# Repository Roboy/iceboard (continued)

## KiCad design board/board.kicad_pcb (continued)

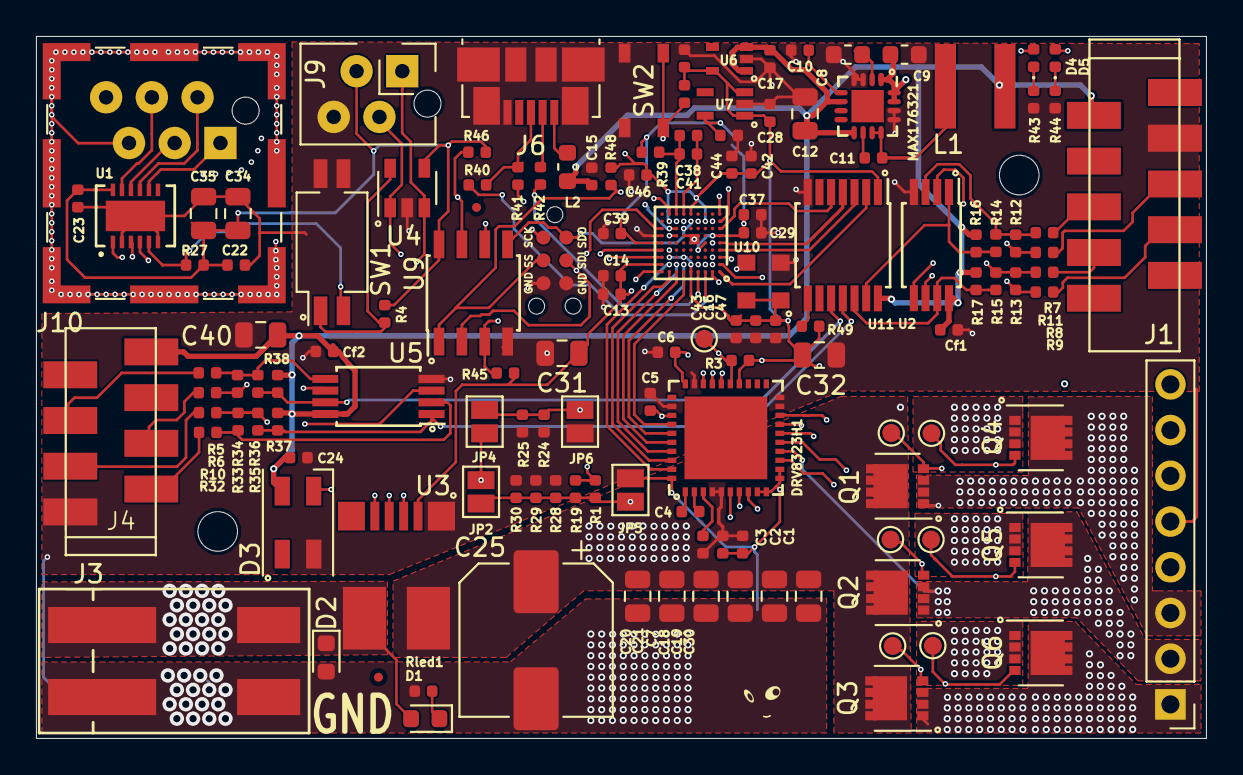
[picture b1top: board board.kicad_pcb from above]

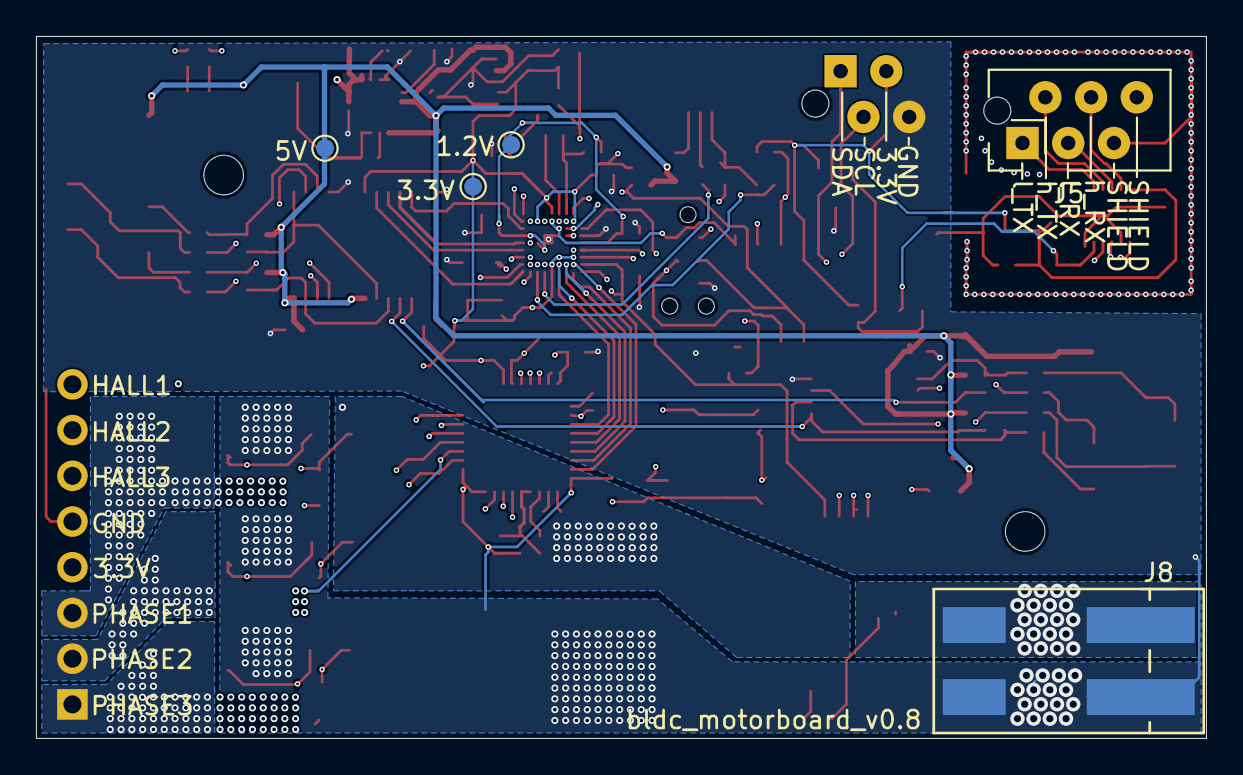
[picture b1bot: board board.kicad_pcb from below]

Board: 4 copper layers, 65.0 x 39.0 mm, 148 parts (5 on the bottom side), 97 nets.

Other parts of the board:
U6#2, U6#3: MIC5504-3.3YM5-TR; SC70-5

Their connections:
+5V: U6#2.1, U6#2.3, U6#3.1, U6#3.3; also elsewhere on the board
GND: U6#2.2, U6#3.2; also elsewhere on the board
unnamed 107: U6#2.4, U6#3.4; also elsewhere on the board

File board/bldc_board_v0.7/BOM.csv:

Id,Designator,Package,Quantity,Designation,Supplier and ref
2,"C35,C34,C32,C31,C40",C_0805_2012Metric,5,100u/6.3V,https://www.mouser.de/ProductDetail/Murata-Electronics/GRM21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
3,U11,TSSOP-14_4.4x5mm_P0.65mm,1,TXB0104PW,https://www.mouser.de/ProductDetail/Texas-Instruments/TXB010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
4,L1,XAL5050-103MEC,1,10uH,https://www.mouser.de/ProductDetail/Coilcraft/XAL5050-103MEC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
6,U8,iCE40-PL9K-CM81,1,iCE40-LP8K-CM81,https://www.mouser.de/ProductDetail/Lattice/iCE40LP8K-CM81?q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
7,J4,micro_match_female_8pos_SMT,1,ENCODER1,https://www.mouser.de/ProductDetail/?qs=tddCKBGf4%252BORyb3A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
8,DRV8323H1,QFN-40-1EP_6x6mm_Pitch0.5mm,1,DRV8323HRTA,https://www.mouser.de/ProductDetail/Texas-Instruments/DRV832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
9,"U2,U5",TSSOP-8_4.4x3mm_P0.65mm,2,LM2903,https://www.mouser.de/ProductDetail/Texas-Instruments/LM2903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
10,"Q2,Q1,Q4,Q5,Q3,Q6",VSON-8_3.3x3.3mm_P0.65mm_NexFET,6,BSZ100N06NS,https://www.mouser.de/ProductDetail/Infineon-Technologies/BS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
11,U1,ltc2855,1,LTC2855CDEPBF,https://www.mouser.de/ProductDetail/Analog-Devices/LTC2855CD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
13,"R27,R15,R14,R4,Rled1,R3,R35,R36,R45,R46,R48,R49,R47",R_0402_1005Metric,21,10k,
14,"C23,C22,C11,Cf1,C6,C2,C24,Cf2,C13,C14,C16,C29,C41,C44,C46,C47",C_0402_1005Metric,16,0.1uF,https://www.mouser.de/ProductDetail/Wurth-Elektronik/8850121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
15,"C21,C19,C18,C27,C20,C7,C30",C_0805_2012Metric,7,22uF/35V,https://www.mouser.de/ProductDetail/TDK/C2012JB1V226M125AC?q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
17,C25,CP_Elec_6.3x4.5,1,220uF,https://www.mouser.de/ProductDetail/Nichicon/UUR1V221MNL6GS?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
18,"C8,C9",C_0603_1608Metric,2,2.2uF,https://www.mouser.de/ProductDetail/Murata-Electronics/GRM18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
19,C12,C_0805_2012Metric,1,22uF,https://www.mouser.de/ProductDetail/KEMET/C0805C226M9PACTU?q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
20,MAX176321,QFN-16-1EP_3x3mm_Pitch0.5mm,1,MAX17632,https://www.mouser.de/ProductDetail/Maxim-Integrated/MAX1763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
21,C10,C_0402_1005Metric,1,5600pF,
22,"R11,R10,R9,R8,R7,R6,R5,R32,R17,R16,R37,R38",R_0402_1005Metric,8,1k,
23,D2,D_0603_1608Metric,1,D_TVS,https://www.mouser.de/ProductDetail/Comchip-Technology/CPDU2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
26,J3,Wago_2060_2_SMD,1,POWER_IN,https://www.reichelt.com/de/en/smd-pcb-terminal-2-pole-rm-4-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
28,"C5,C3,C17,C26,C28,C36",C_0402_1005Metric,6,1uF,
29,C4,C_0402_1005Metric,1,47nF,
30,"C1,C15,C38",C_0402_1005Metric,3,10uF,https://www.mouser.de/ProductDetail/Taiyo-Yuden/GMK316BBJ106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
32,D3,LED_SK6812MINI_PLCC4_3.5x3.5mm_P1.75mm,1,SK6812MINI,https://www.aliexpress.com/item/32434844290.html
38,U3,TLI4970,1,TLI4970,https://www.mouser.de/ProductDetail/Infineon-Technologies/TL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
44,J1,micro_match_female_10pos_SMT,1,ENCODER0,https://www.mouser.de/ProductDetail/TE-Connectivity/1-217871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
45,R39,R_0402_1005Metric,1,100,
46,R40,R_0402_1005Metric,1,1.5k,
47,"R41,R42",R_0402_1005Metric,2,68,
48,"R43,R44",R_0402_1005Metric,2,270,
49,U4,SOT-23-5,1,EEPROM,https://www.mouser.de/ProductDetail/Microchip-Technology-Atm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
52,J6,USB_Micro-B_Molex_47346-0001,1,USB_OTG,https://www.mouser.de/ProductDetail/Molex/47346-0001?qs=sGAE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
53,U9,SOIC-8_3.9x4.9mm_P1.27mm,1,AT25SF081-SSHD-B,https://www.mouser.de/ProductDetail/Adesto-Technologies/AT25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
54,SW2,PTS_810_SMT_Switch,1,SW_Push,https://www.mouser.de/ProductDetail/CK/PTS810SJK250SMTRLFS?q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
55,U6,SC70-5,1,MIC5504-3.3YM5-TR,https://www.mouser.de/ProductDetail/595-TLV70033DCKR
56,U7,SC-70-C5,1,MIC5365-1.2YC5-TR,https://www.mouser.de/ProductDetail/Microchip-Technology-Mic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
57,U10,CDFN3225-4LD-PL-1,1,DSC6001CI2A-016.0000T,https://www.mouser.de/ProductDetail/Microchip-Technology/DSC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
58,"C37,C39,C42,C43",C_0402_1005Metric,4,10nF,
59,D1,LED_0603_1608Metric,1,LED,https://www.mouser.de/ProductDetail/ROHM-Semiconductor/SMLD1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
60,L2,L_0603_1608Metric,1,Bead,https://www.mouser.de/ProductDetail/Murata-Electronics/BLM18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
61,SW1,SW_DIP_SPSTx02_Slide_Copal_CHS-02A_W5.08mm_P1.27mm_JPin,1,SW_DIP_x02,https://www.digikey.de/product-detail/de/nidec-copal-electro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
62,"D4,D5",LED_0402_1005Metric,2,LED_Small,https://www.mouser.de/ProductDetail/ROHM-Semiconductor/SML-P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
,,,114,,

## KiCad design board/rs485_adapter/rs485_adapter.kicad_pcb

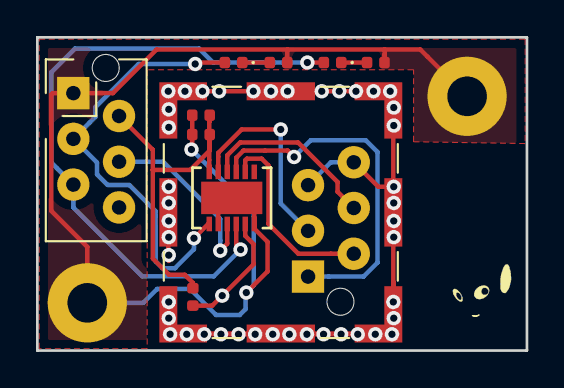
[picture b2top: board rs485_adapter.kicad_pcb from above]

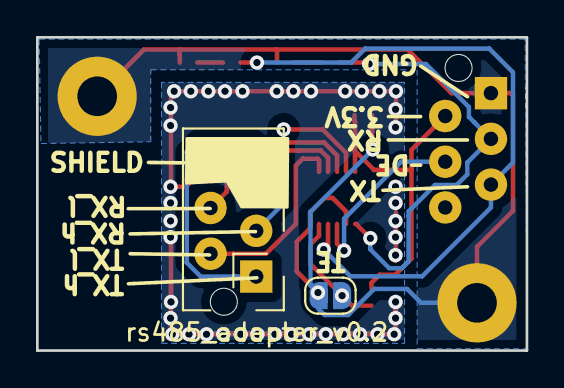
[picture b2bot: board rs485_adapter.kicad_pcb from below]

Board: 2 copper layers, 27.2 x 17.4 mm, 17 parts (2 on the bottom side), 13 nets.

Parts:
C1, C2: 0.1uF; C_0402_1005Metric
D1, D2: LED; LED_0402_1005Metric
H1, H2: MountingHole_Pad; MountingHole_2.2mm_M2_Pad
H3: ears; R1_ear_silk_5.5mm
H4: eyes; R1_eyes_mask_5.5mm
H5: face; R1_face_mask_5.5mm
J1: RF_Shield_Two_Pieces; Laird_Technologies_BMI-S-201-F_13.66x12.70mm
J2: uart; TE-Connectivity_Micro-Match_connector_02x03_Pitch_1.27mm
J3: diff_uart; TE-Connectivity_Micro-Match_connector_02x03_Pitch_1.27mm
JP1: SolderJumper_2_Open; SolderJumper-2_P1.3mm_Open_RoundedPad1.0x1.5mm
R1: 10k; R_0402_1005Metric
R2, R3: 1k; R_0402_1005Metric
U1: LTC2855CDEPBF; ltc2855

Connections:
+3V3: C1.1, C2.1, J2.2, R1.2, U1.12
/DE: J2.4, U1.3
/RX_iso: D2.2, J2.3, U1.1
/TX_iso: D1.2, J2.5, U1.4
/h_Rx: J3.3, U1.11
/h_Tx: J3.1, U1.9
/l_Rx: J3.4, U1.10
/l_Tx: J3.2, U1.8
/term_te: JP1.1, R1.1, U1.5
GND: C1.2, C2.2, H1.1, H2.1, J2.1, JP1.2, R2.1, R3.1, U1.2, U1.6, U1.13
unnamed: D1.1, R2.2
unnamed: D2.1, R3.2
SHIELD: J1.1, J3.5, J3.6

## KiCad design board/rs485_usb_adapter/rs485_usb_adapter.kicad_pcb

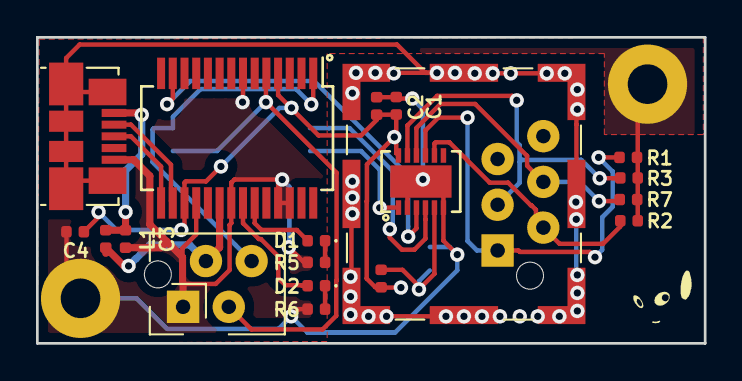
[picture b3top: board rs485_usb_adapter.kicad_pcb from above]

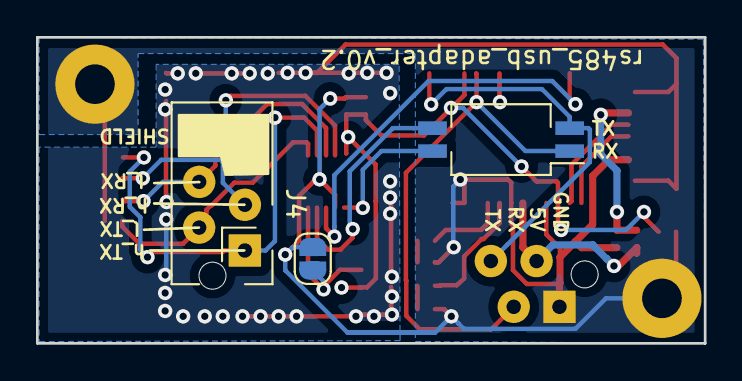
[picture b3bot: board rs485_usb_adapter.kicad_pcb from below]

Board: 2 copper layers, 37.1 x 17.0 mm, 27 parts (3 on the bottom side), 21 nets.

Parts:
C1, C2, C4: 0.1uF; C_0402_1005Metric
C3: 10nF; C_0402_1005Metric
D1, D2: LED; LED_0402_1005Metric
H1, H2: MountingHole_Pad; MountingHole_2.2mm_M2_Pad
H3: ears; R1_ear_silk_5.5mm
H4: eyes; R1_eyes_mask_5.5mm
H5: face; R1_face_mask_5.5mm
J1: USB_OTG; USB_Micro-B_Molex_47346-0001
J2: RF_Shield_Two_Pieces; Laird_Technologies_BMI-S-201-F_13.66x12.70mm
J3: uart; TE-Connectivity_Micro-Match_connector_02x02_Pitch_1.27mm
J4: diff_uart; TE-Connectivity_Micro-Match_connector_02x03_Pitch_1.27mm
JP1: SolderJumper_2_Open; SolderJumper-2_P1.3mm_Open_RoundedPad1.0x1.5mm
L1: Ferrite_Bead_Small; R_0402_1005Metric
R1, R2, R3, R4, R7: 10k; R_0402_1005Metric
R5, R6: 1k; R_0402_1005Metric
SW1: RS485_enable; SW_DIP_SPSTx02_Slide_Copal_CHS-02B_W7.62mm_P1.27mm
U1: LTC2855CDEPBF; ltc2855
U2: FT232RL; SSOP-28_5.3x10.2mm_P0.65mm

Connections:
+3V3: C1.1, C2.1, C4.1, R4.2, U1.12, U2.4, U2.17
+5V: J3.2, L1.1, U2.20
/DE: U1.3, U2.13
/RX_iso: J3.3, SW1.1, U2.5
/TX_iso: J3.4, SW1.2, U2.1
/USB_N: J1.2, U2.16
/USB_P: J1.3, U2.15
/h_Rx: J4.3, R3.2, U1.11
/h_Tx: J4.1, R1.2, U1.9
/l_Rx: J4.4, R7.2, U1.10
/l_Tx: J4.2, R2.2, U1.8
/term_te: JP1.1, R4.1, U1.5
GND: C1.2, C2.2, C3.2, C4.2, H1.1, H2.1, J1.5, J3.1, JP1.2, R1.1, R2.1, R3.1, R5.1, R6.1, R7.1, U1.2, U1.6, U1.13, U2.7, U2.18, U2.21, U2.25, U2.26
unnamed: C3.1, J1.1, L1.2
unnamed: D1.1, R5.2
unnamed: D1.2, U2.23
unnamed: D2.1, R6.2
unnamed: D2.2, U2.22
unnamed: SW1.3, U1.4
unnamed: SW1.4, U1.1
SHIELD: J1.6, J2.1, J4.5, J4.6

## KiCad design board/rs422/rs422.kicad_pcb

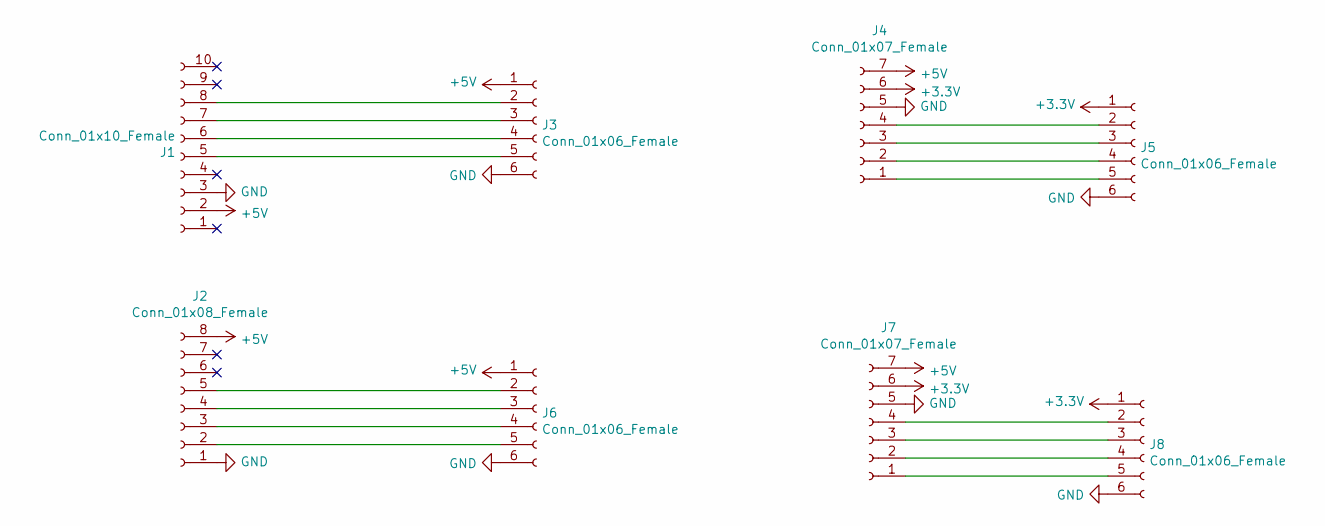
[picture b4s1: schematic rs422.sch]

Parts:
J1: Conn_01x10_Female; micro_match_female_10pos_SMT
J2: Conn_01x08_Female; micro_match_female_8pos_SMT
J3, J5, J6, J8: Conn_01x06_Female; PinSocket_1x06_P2.54mm_Vertical
J4, J7: Conn_01x07_Female; PinSocket_1x07_P2.54mm_Vertical

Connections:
+3V3: J4.6, J5.1, J7.6, J8.1
+5V: J1.2, J2.8, J3.1, J4.7, J6.1, J7.7
GND: J1.3, J2.1, J3.6, J4.5, J5.6, J6.6, J7.5, J8.6
unnamed: J1.5, J3.5
unnamed: J1.6, J3.4
unnamed: J1.7, J3.3
unnamed: J1.8, J3.2
unnamed: J2.2, J6.5
unnamed: J2.3, J6.4
unnamed: J2.4, J6.3
unnamed: J2.5, J6.2
unnamed: J4.1, J5.5
unnamed: J4.2, J5.4
unnamed: J4.3, J5.3
unnamed: J4.4, J5.2
unnamed: J7.1, J8.5
unnamed: J7.2, J8.4
unnamed: J7.3, J8.3
unnamed: J7.4, J8.2

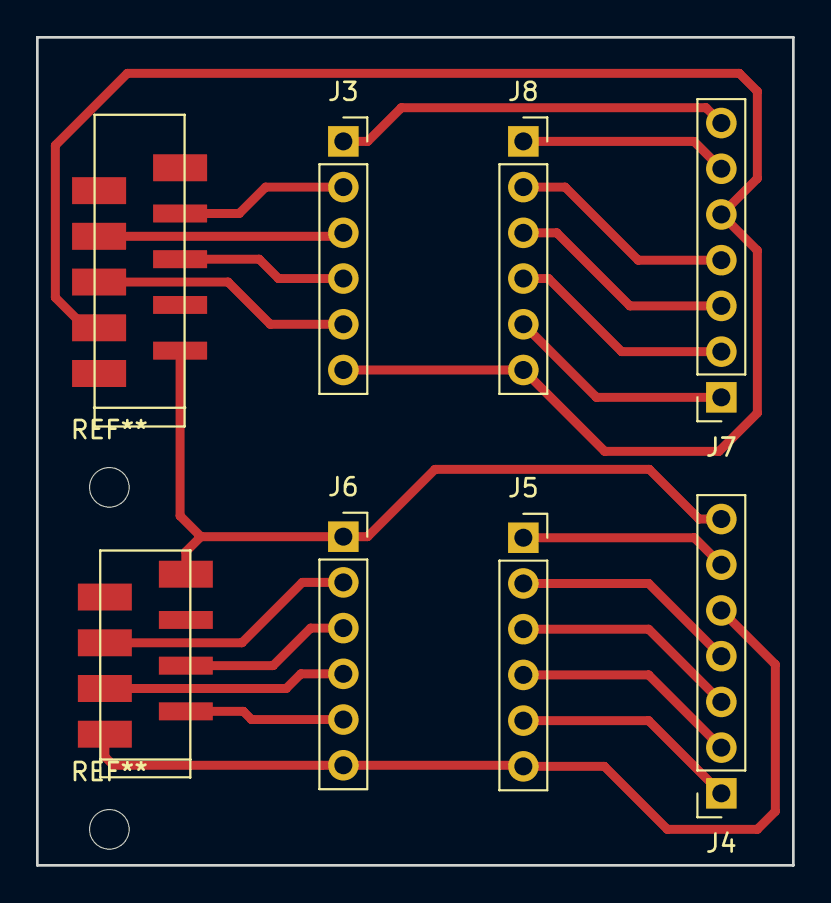
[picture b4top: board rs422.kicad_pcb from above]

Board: 2 copper layers, 42.0 x 46.0 mm, 8 parts (0 on the bottom side), 19 nets.

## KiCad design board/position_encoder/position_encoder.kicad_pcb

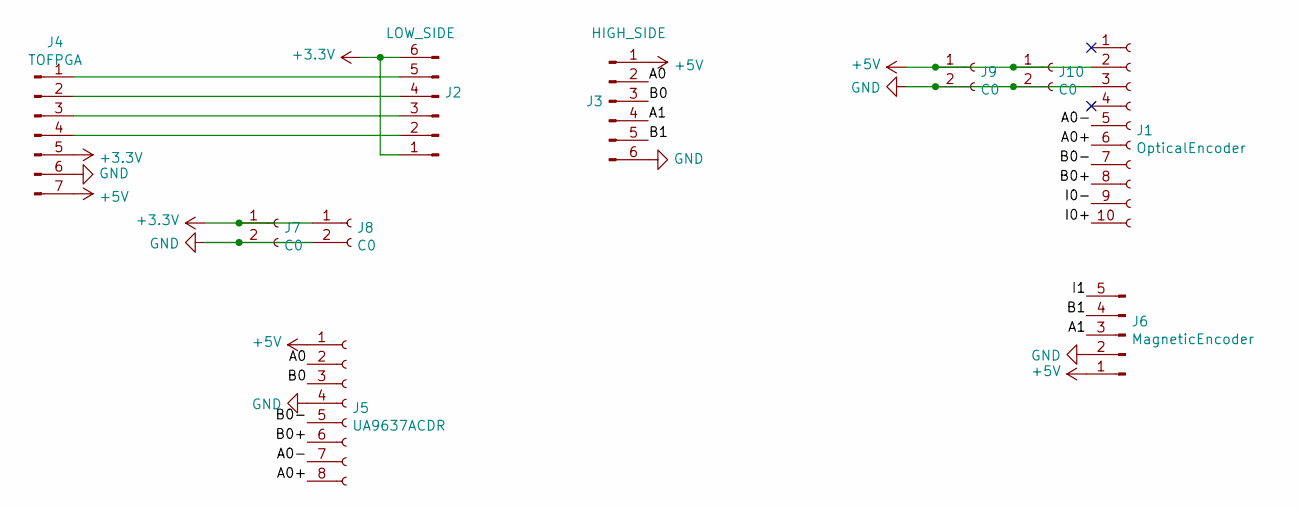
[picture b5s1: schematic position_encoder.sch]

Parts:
J1: OpticalEncoder; PinSocket_1x10_P2.54mm_Vertical
J2: LOW_SIDE; PinSocket_1x06_P2.54mm_Vertical
J3: HIGH_SIDE; PinSocket_1x06_P2.54mm_Vertical
J4: TOFPGA; PinSocket_1x07_P2.54mm_Vertical
J5: UA9637ACDR; SOIC-8_3.9x4.9mm_P1.27mm
J6: MagneticEncoder; PinHeader_1x05_P2.54mm_Vertical
J7, J8, J9, J10: C0; PinHeader_1x02_P2.54mm_Vertical

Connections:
+3V3: J2.1, J2.6, J4.5, J7.1, J8.1
+5V: J1.2, J3.1, J4.7, J5.1, J6.1, J9.1, J10.1
/A0: J3.2, J5.2
/A0+: J1.6, J5.8
/A0-: J1.5, J5.7
/A1: J3.4, J6.3
/B0: J3.3, J5.3
/B0+: J1.8, J5.6
/B0-: J1.7, J5.5
/B1: J3.5, J6.4
/I0+: J1.10
/I0-: J1.9
/I1: J6.5
GND: J1.3, J3.6, J4.6, J5.4, J6.2, J7.2, J8.2, J9.2, J10.2
unnamed: J2.2, J4.4
unnamed: J2.3, J4.3
unnamed: J2.4, J4.2
unnamed: J2.5, J4.1

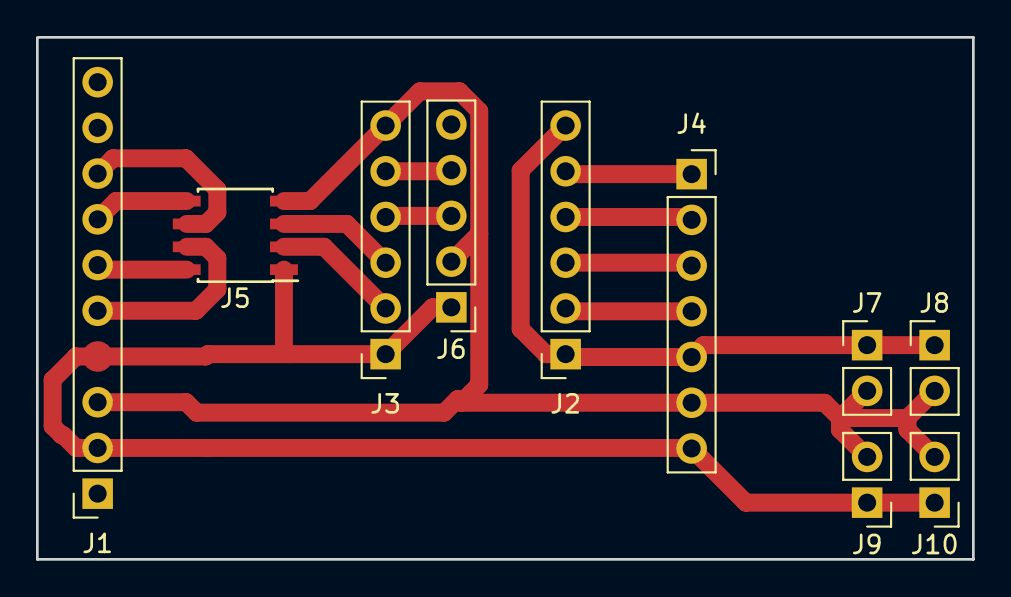
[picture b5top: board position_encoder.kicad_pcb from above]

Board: 2 copper layers, 52.0 x 29.0 mm, 10 parts (0 on the bottom side), 15 nets.

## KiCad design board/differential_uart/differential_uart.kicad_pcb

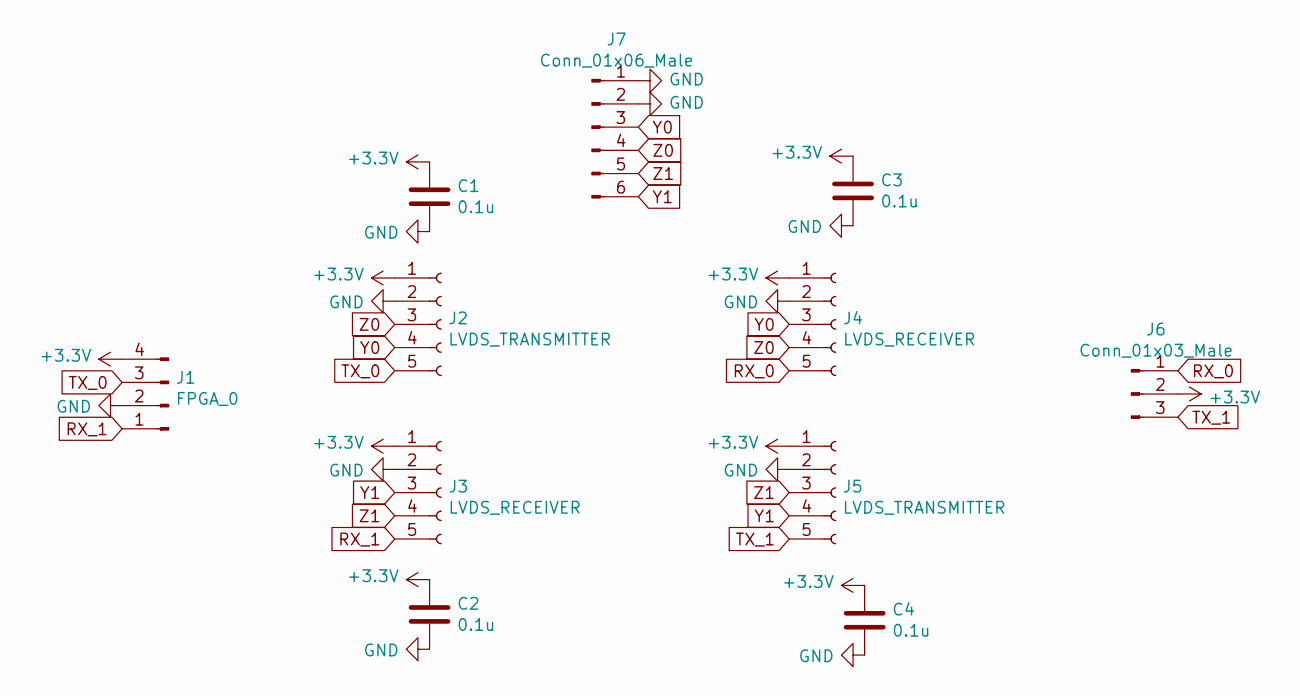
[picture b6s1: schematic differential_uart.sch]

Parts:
C1, C2, C3, C4: 0.1u; C_01005_0402Metric
J1: FPGA_0; PinHeader_1x04_P2.54mm_Vertical
J2, J5: LVDS_TRANSMITTER; SOT-23-5
J3, J4: LVDS_RECEIVER; SOT-23-5
J6: Conn_01x03_Male; PinHeader_1x03_P2.54mm_Vertical
J7: Conn_01x06_Male; PinHeader_1x06_P2.54mm_Vertical

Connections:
+3V3: C1.1, C2.1, C3.1, C4.1, J1.4, J2.1, J3.1, J4.1, J5.1, J6.2
GND: C1.2, C2.2, C3.2, C4.2, J1.2, J2.2, J3.2, J4.2, J5.2, J7.1, J7.2
RX_0: J4.5, J6.1
RX_1: J1.1, J3.5
TX_0: J1.3, J2.5
TX_1: J5.5, J6.3
Y0: J2.4, J4.3, J7.3
Y1: J3.3, J5.4, J7.6
Z0: J2.3, J4.4, J7.4
Z1: J3.4, J5.3, J7.5

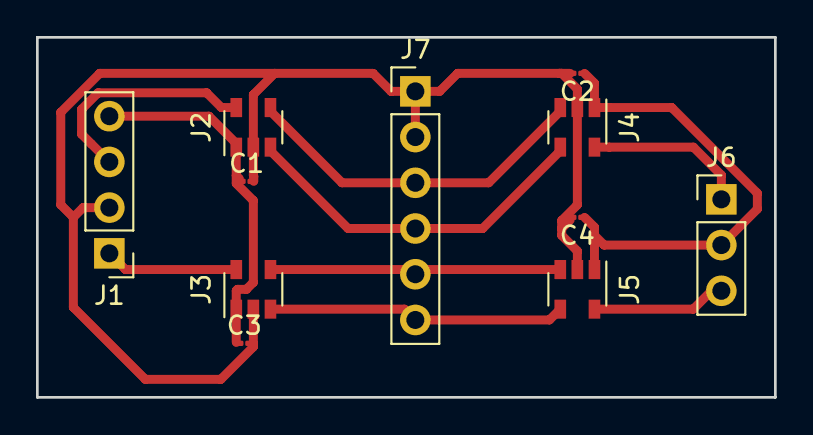
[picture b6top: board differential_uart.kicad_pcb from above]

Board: 2 copper layers, 41.0 x 20.0 mm, 11 parts (0 on the bottom side), 10 nets.

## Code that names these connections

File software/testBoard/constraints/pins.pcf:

# ##############################################################################

# iCEcube PCF

# Version:            2017.01.27914

# File Generated:     Jun 24 2017 13:04:57

# Family & Device:    iCE40LP8K

# Package:            CM81

# ##############################################################################

###IOSet List 24
set_io CLK B2
set_io LED B3
set_io USBPU A3
set_io ENCODER0_A A1
set_io ENCODER0_B D1
set_io ENCODER1_A E1
set_io ENCODER1_B G1
set_io HALL1 B1
set_io HALL2 C1
set_io HALL3 C2
set_io FAULT_N A2
set_io NEOPXL E2
set_io DE H1
set_io TX J1
set_io RX H2
set_io CS_CLK G9
set_io CS D8
set_io CS_MISO D9
set_io SCL C9
set_io SDA A9
set_io INLC B8
set_io INHC A8
set_io INLB B7
set_io INHB A7
set_io INLA B6
set_io INHA A6

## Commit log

2019-09-22 initial
2019-09-22 with correct pinout for v0.3
2019-09-23 v0.4 ordered on pcbway
2019-10-01 with v0.4 pin assignement
2019-10-01 ok the hall sensors are switched, FIX this next revision!
2019-10-01 no news on the commutation front
2019-10-04 fixed commutation for v0.4
2019-10-04 encoder works aswell
2019-10-04 fixed pwmlimit issue in motorcontroller
2019-10-04 with neopixel
2019-10-05 next version
2019-10-06 layout done
2019-10-11 with rf shield
2019-10-11 with inductor
2019-10-11 ground optimisation
2019-10-12 v0.5
2019-10-14 with more pics
2019-10-21 with new pinout
2019-10-22 wtf i have not idea why it turns
2019-10-23 lets use 1xPWM shall we
2019-10-23 works with v0.5
2019-10-23 with correct direction for encoder 0
2019-10-27 with id
2019-10-28 with colored id
2019-10-29 ignoring id for now
2019-10-30 with 16 bit gains
2019-11-20 with ltc422 driver enable fix and more diff comparators for the other encoder aswell
2019-11-21 layout also done
2019-12-05 drive enable bug fixed
2019-12-09 with ice40 on board
2019-12-10 with level shifter
2019-12-12 more progress on layout
2019-12-15 ready to review
2019-12-16 final touch
2019-12-16 with bom
2019-12-20 revised after pcbway input
2019-12-23 updated nothing
2020-01-02 with current sensor read out draft
2020-01-05 updated position file
2020-01-06 with new pin assignements and neopxl control
2020-01-23 it turns, coms are up
2020-01-24 with flash script
2020-01-27 all ids
2020-01-28 with all ids
2020-01-28 with blocking pi controller
2020-01-29 draft i2c eeprom
2020-01-29 draft eeprom i2c readout
2020-01-29 with reading eeprom
2020-01-29 reading eeprom every second
2020-01-29 with intial eeprom read not working for some reason
2020-01-30 oh man, finally...
2020-01-30 sampling on positive edge...
2020-01-30 less timeout
2020-01-31 with better quad decoder
2020-01-31 with correct encoder1 scale
2020-02-03 1MHz
2020-02-04 manual override
2020-02-04 still positive rotation causes problems
2020-02-06 only one direction allowed
2020-02-17 fixed ph phase lock on slow velocities
2020-02-17 with tli4970 readout
2020-02-17 with current sensor readout
2020-02-17 fixed neopixel bitorder
2020-02-17 both directions
2020-02-17 with current limit
2020-02-24 pin control check
2020-02-24 with cross talk check
2020-02-24 with flash test pins
2020-02-24 with image
2020-02-26 rs485 converter
2020-02-26 with panels ordered from aisler
2020-02-26 better controller
2020-02-28 faster and more frequent current readout
2020-03-06 fucking finally
2020-03-09 2MHz working
2020-03-09 integrated variable baudrate into motorboard
2020-03-09 with protocol documentation
2020-03-21 with adc_lvds
2020-03-24 simple integrator
2020-04-04 different fpga footprint, fix of bugs that came up in v0.7
2020-04-13 updated BOM
2020-04-14 with panel
2020-04-15 U8 according to lattice recommendations
2020-04-16 v0.8.1
2020-04-16 v0.8.2
2020-04-17 v0.8.3
2020-04-29 with designators on silkscreen
2020-05-04 adapter for correct wiring and optional uart switch
2020-05-04 adapter for correct wiring
2020-05-08 minor solder mask modifications and better export parameters for solder mask clearance
2020-05-19 without encoder match
2020-05-19 scaled up instead of down
2020-05-19 up to track with master
2020-05-21 better scale factor to 4096 for both encoders er revolution
2020-07-29 2MHZ
2020-07-29 pi controller error divided by 16, which enables smaller gains
2020-07-29 with 0 debounce for the encoders
2020-09-08 with direct_pwm bypass
2020-09-08 with pwmlimit also for direct_pwm
2021-04-07 Small improvement to the messages printed by the arduino eeprom flashing utility. Exported a pdf for the board schematic.
2021-04-07 Added useful script to start the icecube IDE.
2021-04-07 Changed encoder scaling calculation. They are now brought to their minimum common multiple. Created local parameter for gear ratio since code might get used for different motor configurations in the 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
2021-12-06 change the calculation from div53 to mul53 in scaked encoder calculation
2021-12-06 compiled
2021-12-07 new compiled fast
2021-12-10 changed back to div and encoder0 and encoder1 values publish the raw data this was done as a fast compile
2022-01-14 reverted to original roboy3 branch commit 7051a6a and change the debounce_time of the quadrature_decoder to 16
2022-01-17 fast compile raw encoder values, no LED, no Neopixle, Worst case max clock speed 3.74MHz
2022-01-17 uncommented direction otherwise not working
2022-01-20 new software with new scaling of encoder0 and encoder1 because of different gear ratio now (3375/64)
2022-02-01 fixed typo so e1 is published right and compiled new version
2022-02-15 Revert "Roboy3 mul instead of div"
2022-02-16 set debouncetime to 50_000
2022-03-31 fixed length control sorry forgot to push
